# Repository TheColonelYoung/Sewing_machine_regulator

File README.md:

# Electrical regulator for sewing machine
Based on design from: [Robov elektro](http://www.robov.elektro.szm.com/slapka/index.htm)

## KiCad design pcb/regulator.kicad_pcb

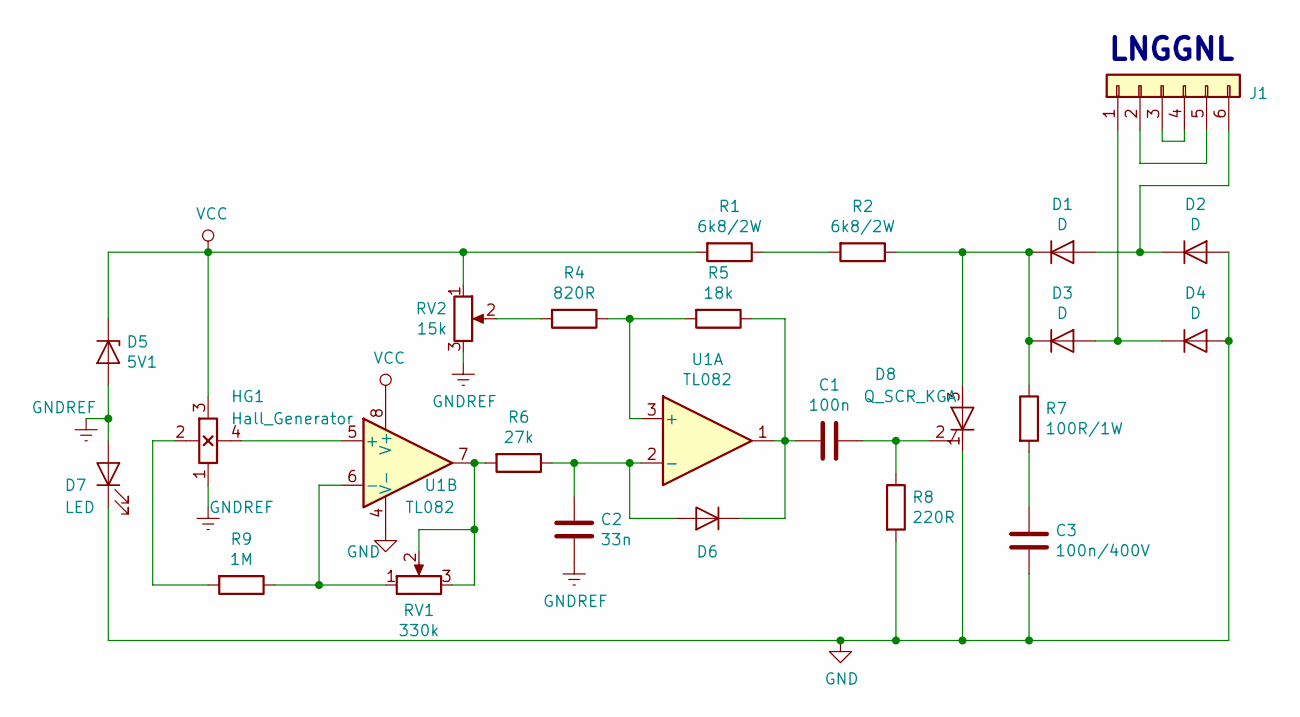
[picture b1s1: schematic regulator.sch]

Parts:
C1: 100n; C_Disc_D7.0mm_W2.5mm_P5.00mm
C2: 33n; C_Disc_D7.0mm_W2.5mm_P5.00mm
C3: 100n/400V; C_Rect_L18.0mm_W7.0mm_P15.00mm_FKS3_FKP3
D1, D2, D3, D4: D; D_DO-15_P12.70mm_Horizontal
D5: 5V1; D_DO-41_SOD81_P7.62mm_Horizontal
D6: D; D_DO-35_SOD27_P7.62mm_Horizontal
D7: LED; LED_D5.0mm
D8: Q_SCR_KGA; TO-39-3
HG1: Hall_Generator; PinHeader_1x04_P2.54mm_Vertical
J1: Conn_01x06; TerminalBlock_bornier-6_P5.08mm
R1, R2: 6k8/2W; R_Axial_DIN0918_L18.0mm_D9.0mm_P22.86mm_Horizontal
R4: 820R; R_Axial_DIN0207_L6.3mm_D2.5mm_P10.16mm_Horizontal
R5: 18k; R_Axial_DIN0207_L6.3mm_D2.5mm_P10.16mm_Horizontal
R6: 27k; R_Axial_DIN0207_L6.3mm_D2.5mm_P10.16mm_Horizontal
R7: 100R/1W; R_Axial_DIN0614_L14.3mm_D5.7mm_P15.24mm_Horizontal
R8: 220R; R_Axial_DIN0207_L6.3mm_D2.5mm_P10.16mm_Horizontal
R9: 1M; R_Axial_DIN0207_L6.3mm_D2.5mm_P10.16mm_Horizontal
RV1: 330k; Potentiometer_Bourns_3339P_Vertical
RV2: 15k; Potentiometer_Bourns_3339P_Vertical
U1: TL082; DIP-8_W7.62mm

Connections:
GND: C3.2, D2.2 (A), D4.2 (A), D7.1 (K), D8.1 (K), R8.2, U1.4 (V-)
GNDREF: C2.2, D5.2 (A), D7.2 (A), HG1.1 (U2), RV2.3
unnamed: C1.1, D8.2 (G), R8.1
unnamed: C1.2, D6.1 (K), R5.1, U1.1
unnamed: C2.1, D6.2 (A), R6.1, U1.2 (-)
unnamed: C3.1, R7.2
unnamed: D1.1 (K), D3.1 (K), D8.3 (A), R2.1, R7.1
unnamed: D1.2 (A), D2.1 (K), J1.6
unnamed: D3.2 (A), D4.1 (K), J1.1
unnamed: HG1.2 (UH1), R9.2
unnamed: HG1.4 (UH2), U1.5 (+)
unnamed: J1.2, J1.5
unnamed: J1.3, J1.4
unnamed: R1.1, R2.2
unnamed: R4.1, R5.2, U1.3 (+)
unnamed: R4.2, RV2.2
unnamed: R6.2, RV1.2, RV1.3, U1.7
unnamed: R9.1, RV1.1, U1.6 (-)
VCC: D5.1 (K), HG1.3 (U1), R1.2, RV2.1, U1.8 (V+)

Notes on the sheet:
LNGGNL

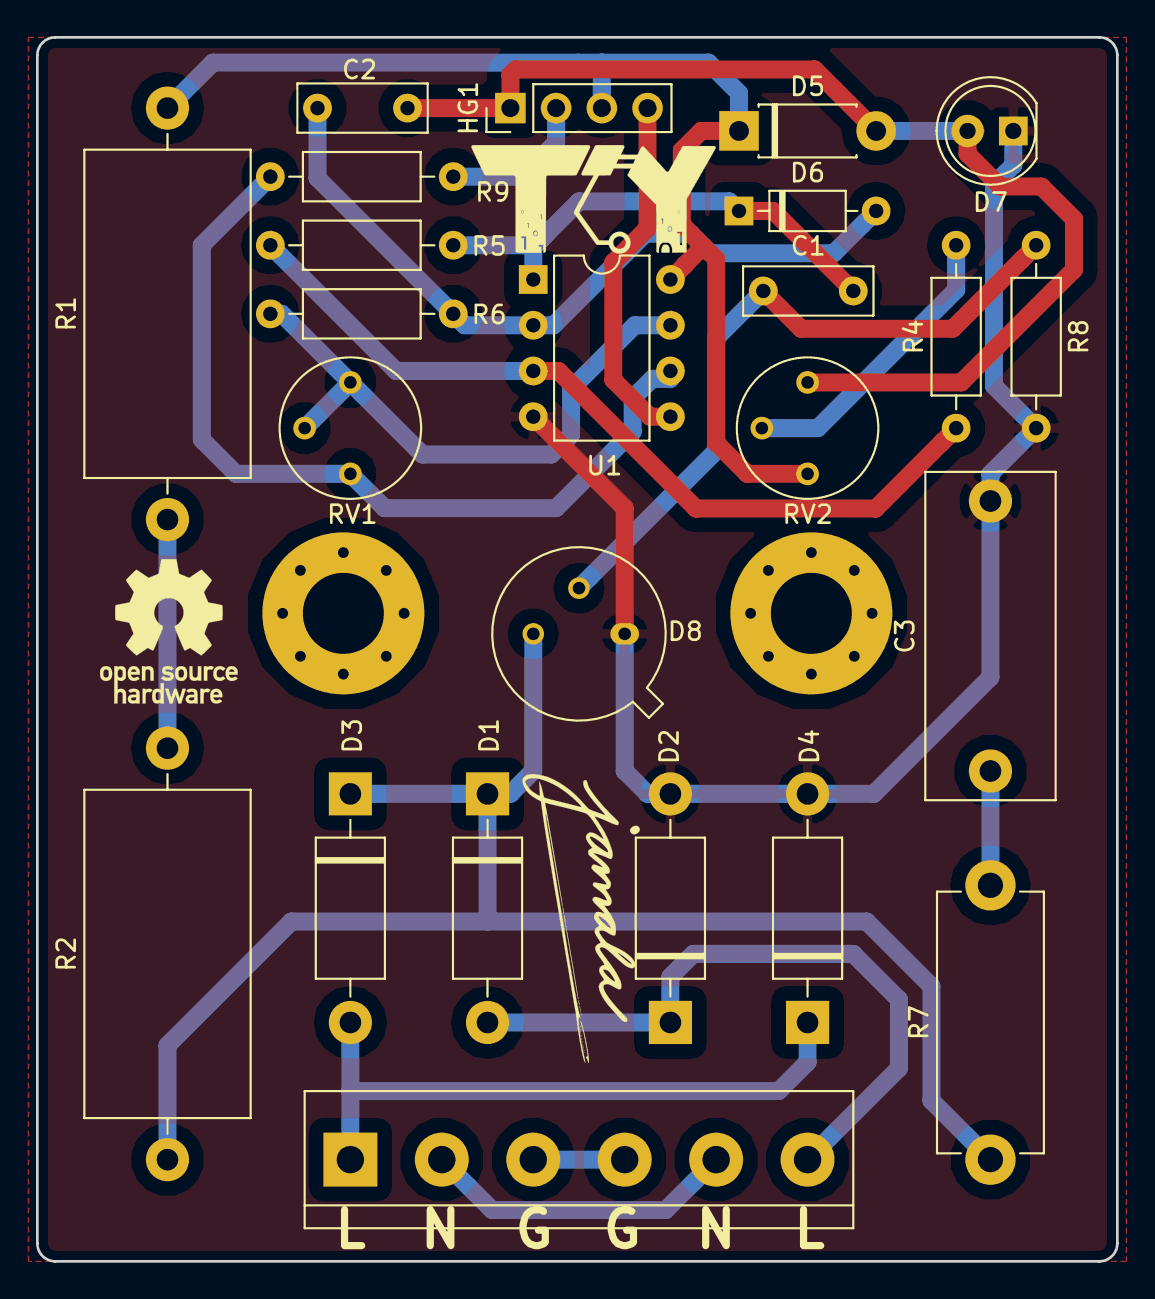
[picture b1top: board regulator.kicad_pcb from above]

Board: 2 copper layers, 60.0 x 68.0 mm, 24 parts (0 on the bottom side), 19 nets.

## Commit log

2018-12-26 Updated README, added outlines for PCB
2018-12-26 Add Kicad project and create schematic for board
2018-12-26 Update of schematics, generated net list
2018-12-26 PCB routing, need to polish
2019-02-04 Updated file structure, added logos to board, cleanup of schematics
2019-02-11 Update QR code, exchange of mounting hole (add vias to outline)
2019-02-11 Add .zip with gerber files for fabrications
